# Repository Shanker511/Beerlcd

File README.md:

# The Beer LCD

The Beer Lcd is a project desgined to help the Homebrewer keep track of the temp of the fermenter.

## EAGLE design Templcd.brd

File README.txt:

The Beer Lcd is a project desgined to help the Homebrewer keep tack of the tem of the fermenter.

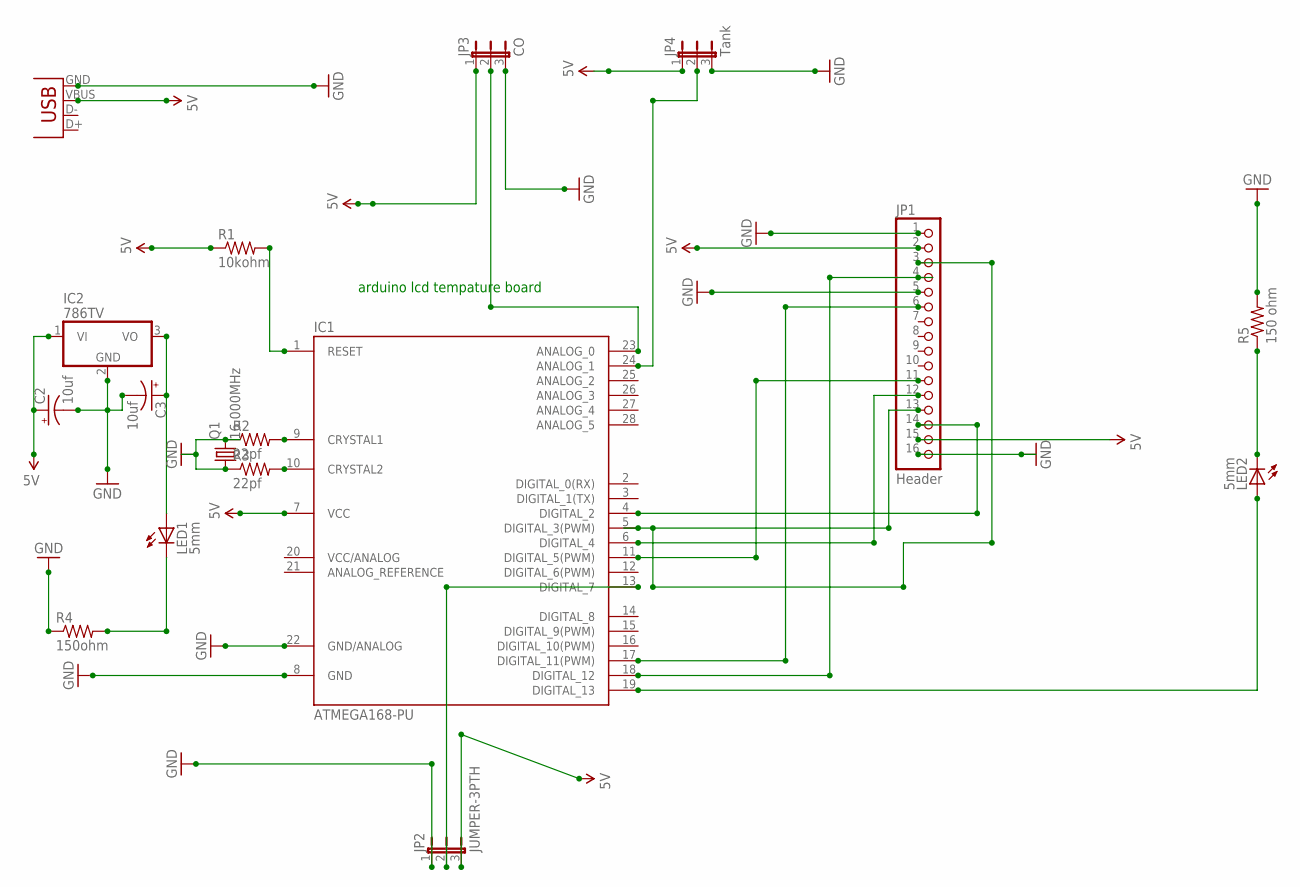
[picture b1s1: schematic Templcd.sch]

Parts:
C2, C3: 10uf; CPOL-RADIAL-100UF-25V
IC1: ATMEGA168-PU; DIL28-3
IC2: 786TV; TO220V
JP1: Header; 1X16
JP2: JUMPER-3PTH; 1X03
JP3: CO; JP2W
JP4: Tank; JP2W
LED1, LED2: 5mm; LED5MM
Q1: 16.000MHz; HC49U-V
R1: 10kohm; AXIAL-0.3
R2, R3: 22pf; AXIAL-0.3
R4: 150ohm; AXIAL-0.3
R5: 150 ohm; AXIAL-0.3
X1: USBPTH; USB-B-PTH

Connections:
5V: C2.1 (+), IC1.7 (VCC), IC2.1 (VI), JP1.2, JP1.15, JP2.3, JP3.1, JP4.1, R1.P$1 (1), X1.VBUS
GND: C2.2 (-), C3.2 (-), IC1.8 (GND), IC1.22 (GND/ANALOG), IC2.2 (GND), JP1.1, JP1.5, JP1.16, JP2.1, JP3.3, JP4.3, Q1.1, Q1.2, R2.P$1 (1), R3.P$1 (1), R4.P$1 (1), R5.P$2 (2), X1.GND
unnamed: LED1.K (C), R4.P$2 (2)
unnamed: IC1.9 (CRYSTAL1), R2.P$2 (2)
unnamed: IC1.18 (DIGITAL_12), JP1.4
unnamed: IC1.17 (DIGITAL_11(PWM)), JP1.6
unnamed: IC1.11 (DIGITAL_5(PWM)), JP1.11
unnamed: IC1.6 (DIGITAL_4), JP1.12
unnamed: IC1.5 (DIGITAL_3(PWM)), JP1.3, JP1.13
unnamed: IC1.4 (DIGITAL_2), JP1.14
unnamed: IC1.10 (CRYSTAL2), R3.P$2 (2)
unnamed: IC1.1 (RESET), R1.P$2 (2)
unnamed: IC1.23 (ANALOG_0), JP3.2
unnamed: IC1.13 (DIGITAL_7), JP2.2
unnamed: C3.1 (+), IC2.3 (VO), LED1.A
unnamed: IC1.24 (ANALOG_1), JP4.2
unnamed: IC1.19 (DIGITAL_13), LED2.A
unnamed: LED2.K (C), R5.P$1 (1)

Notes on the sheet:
arduino lcd tempature board

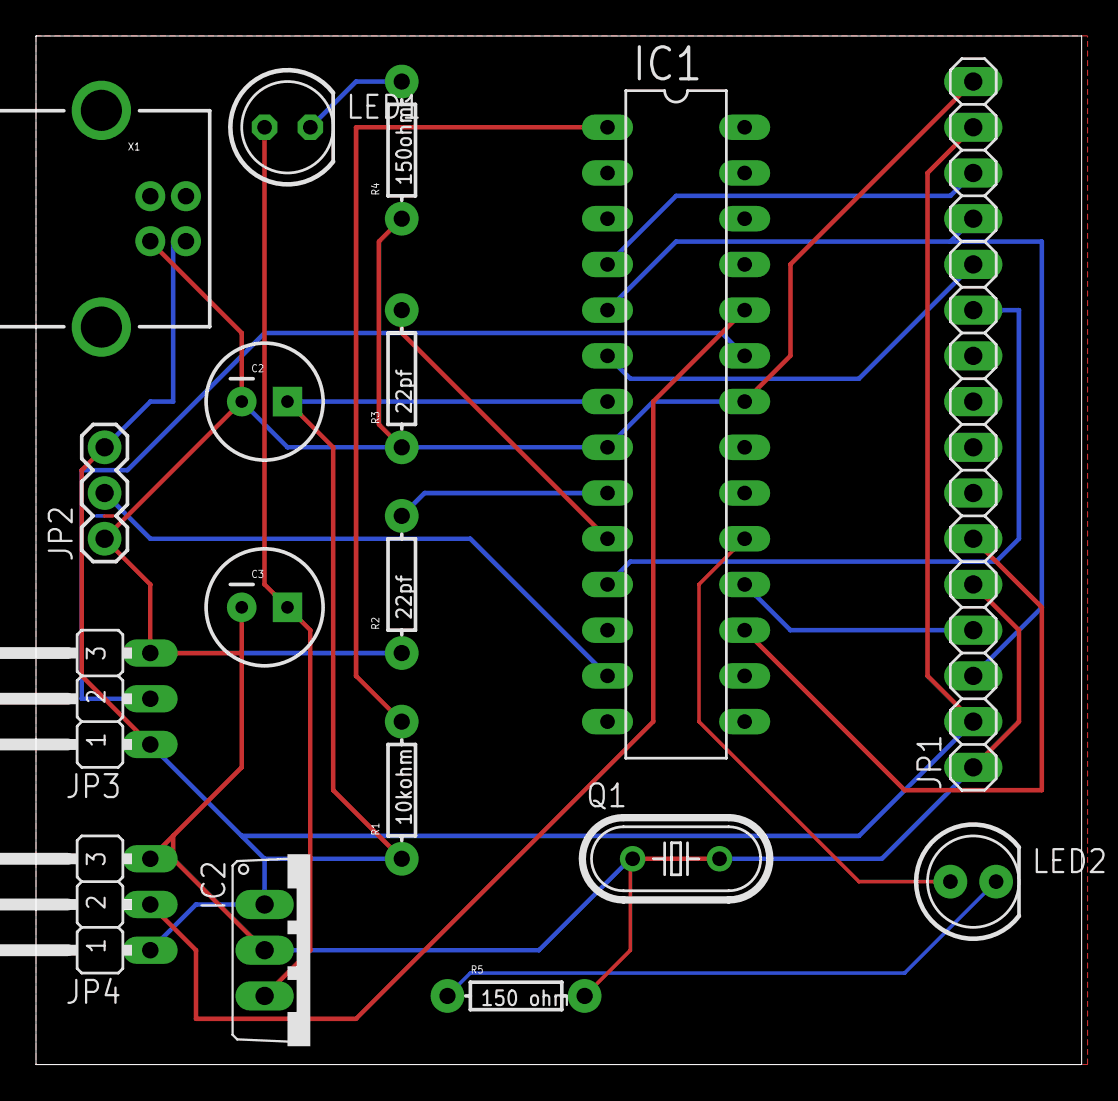
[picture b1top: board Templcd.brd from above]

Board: 2 copper layers, 58.1 x 57.1 mm, 17 parts (0 on the bottom side), 18 nets.

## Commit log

2013-02-09 fist commit
2013-02-09 adding entire project
2013-02-12 removing trash
2013-02-12 Changed to README.md
